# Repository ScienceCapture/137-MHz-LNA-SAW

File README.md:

# 137-MHz-LNA-SAW

By using a simple double-crossed or QFH antenna it is possible to detect and record the transmission of the NOAA and Meteor-M2 weather satellites. This signal can be received and then decoded into a detailed image of the Earth taken from space! Its quality however, is directly determined by the signal strength. This is where the 137-MHz-LNA-SAW comes into play! The integrated low noise amplifier (LNA) makes the weak signal much stronger. It is then passed through the SAW filter with attenuates all of the unwanted frequencies with a steep cutoff region. The device was designed with ESD safety in mind and features a USB-C port to power the amplifier.

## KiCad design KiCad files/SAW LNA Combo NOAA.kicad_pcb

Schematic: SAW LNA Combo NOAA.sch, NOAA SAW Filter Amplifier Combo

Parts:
C1, C3, C4, C5: 96pF; C_0805_2012Metric
C2: 96nF; C_0805_2012Metric
C6: 10pF; C_0805_2012Metric
C7, C9: 1uF; C_0805_2012Metric
C8: 100uF; CP_Elec_6.3x5.8
D1, D2, D3: D_TVS; D_0201_0603Metric
D4: LED; LED_0805_2012Metric
J1, J2: Conn_Coaxial; SMA_Amphenol_132289_EdgeMount
L1, L2, L4: 14nH; L_0402_1005Metric
L3: 1.4uH; L_1008_2520Metric_Pad1.43x2.20mm_HandSolder
P1: USB_C_Plug_USB2.0; USB_C_Receptacle_Amphenol_12401610E4-2A
R1: 350R; R_0603_1608Metric
U1: ZLDO500; SO-8_5.3x6.2mm_P1.27mm
U2: SPF5189Z; SOT-89-3
U3: SF2059B-1

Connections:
+5V: C5.2, L3.1, L4.2
GND: C2.1, C3.1, C5.1, C7.1, C8.2, C9.1, D1.2 (A2), D2.2 (A2), D3.2 (A2), D4.1 (K), J1.2 (Ext), J2.2 (Ext), P1.A1 (GND), P1.A12 (GND), P1.B1 (GND), P1.B12 (GND), P1.S1 (SHIELD), U1.2, U1.7, U2.2 (GND), U3.1, U3.2, U3.3, U3.4, U3.6, U3.7, U3.8, U3.9; also elsewhere on the board
unnamed: C1.1, L1.1
unnamed: C1.2, D1.1 (A1), J1.1 (In)
unnamed 4: C2.2, C8.1, C9.2, D2.1 (A1), P1.A4 (VBUS), P1.A9 (VBUS), P1.B4 (VBUS), P1.B9 (VBUS), R1.1, U1.3; also elsewhere on the board
unnamed: C3.2, L2.2, L4.1
unnamed: C4.1, U3.10
unnamed: C4.2, L3.2, U2.3
unnamed: C6.1, C7.2, L2.1, U1.5
unnamed: C6.2, U1.8
unnamed: D3.1 (A1), J2.1 (In), U3.5
unnamed: D4.2 (A), R1.2
unnamed: L1.2, U2.1

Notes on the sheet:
Rainbow happy vibes
3671333 Wurth Elektronik Shield

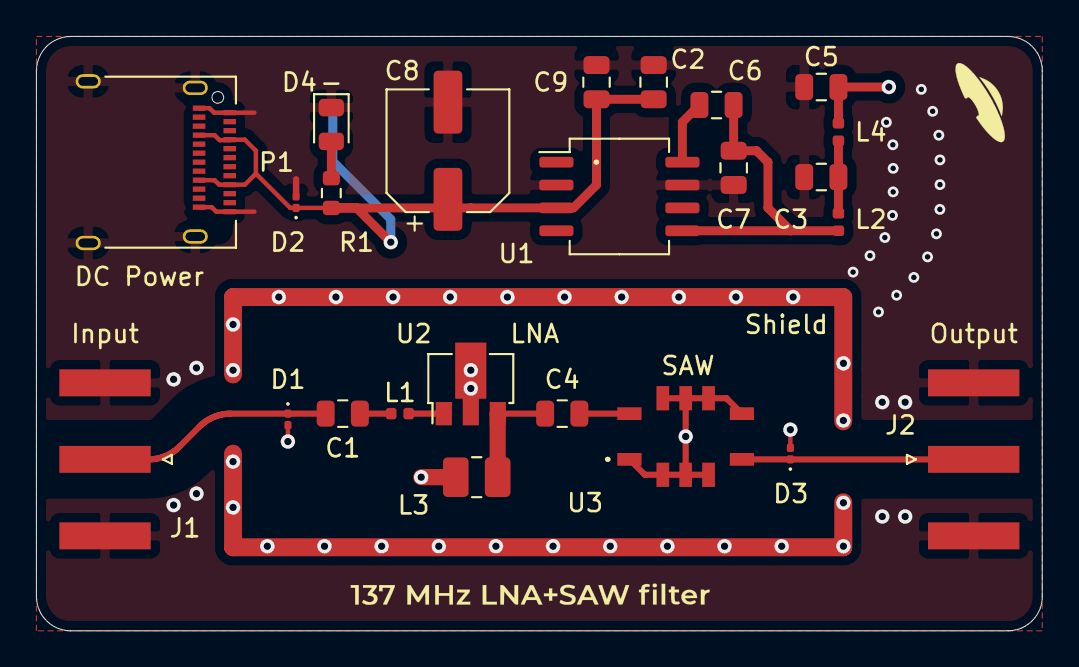
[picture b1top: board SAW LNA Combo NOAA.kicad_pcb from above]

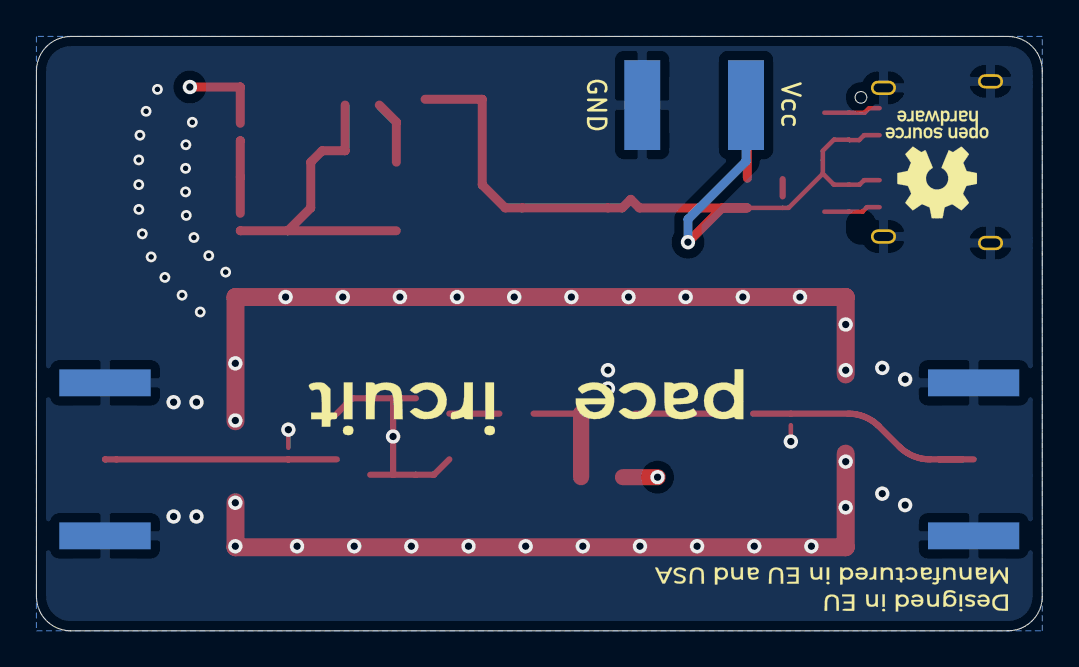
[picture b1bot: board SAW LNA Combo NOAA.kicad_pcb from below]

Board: 4 copper layers, 55.9 x 33.0 mm, 27 parts (2 on the bottom side), 13 nets.

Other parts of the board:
GND: Pad_small
Shield: RF_Guard_Ring_SAW_NOAA
Vcc: Pad_small

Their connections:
GND: GND.1; also elsewhere on the board
unnamed 4: Vcc.1; also elsewhere on the board
